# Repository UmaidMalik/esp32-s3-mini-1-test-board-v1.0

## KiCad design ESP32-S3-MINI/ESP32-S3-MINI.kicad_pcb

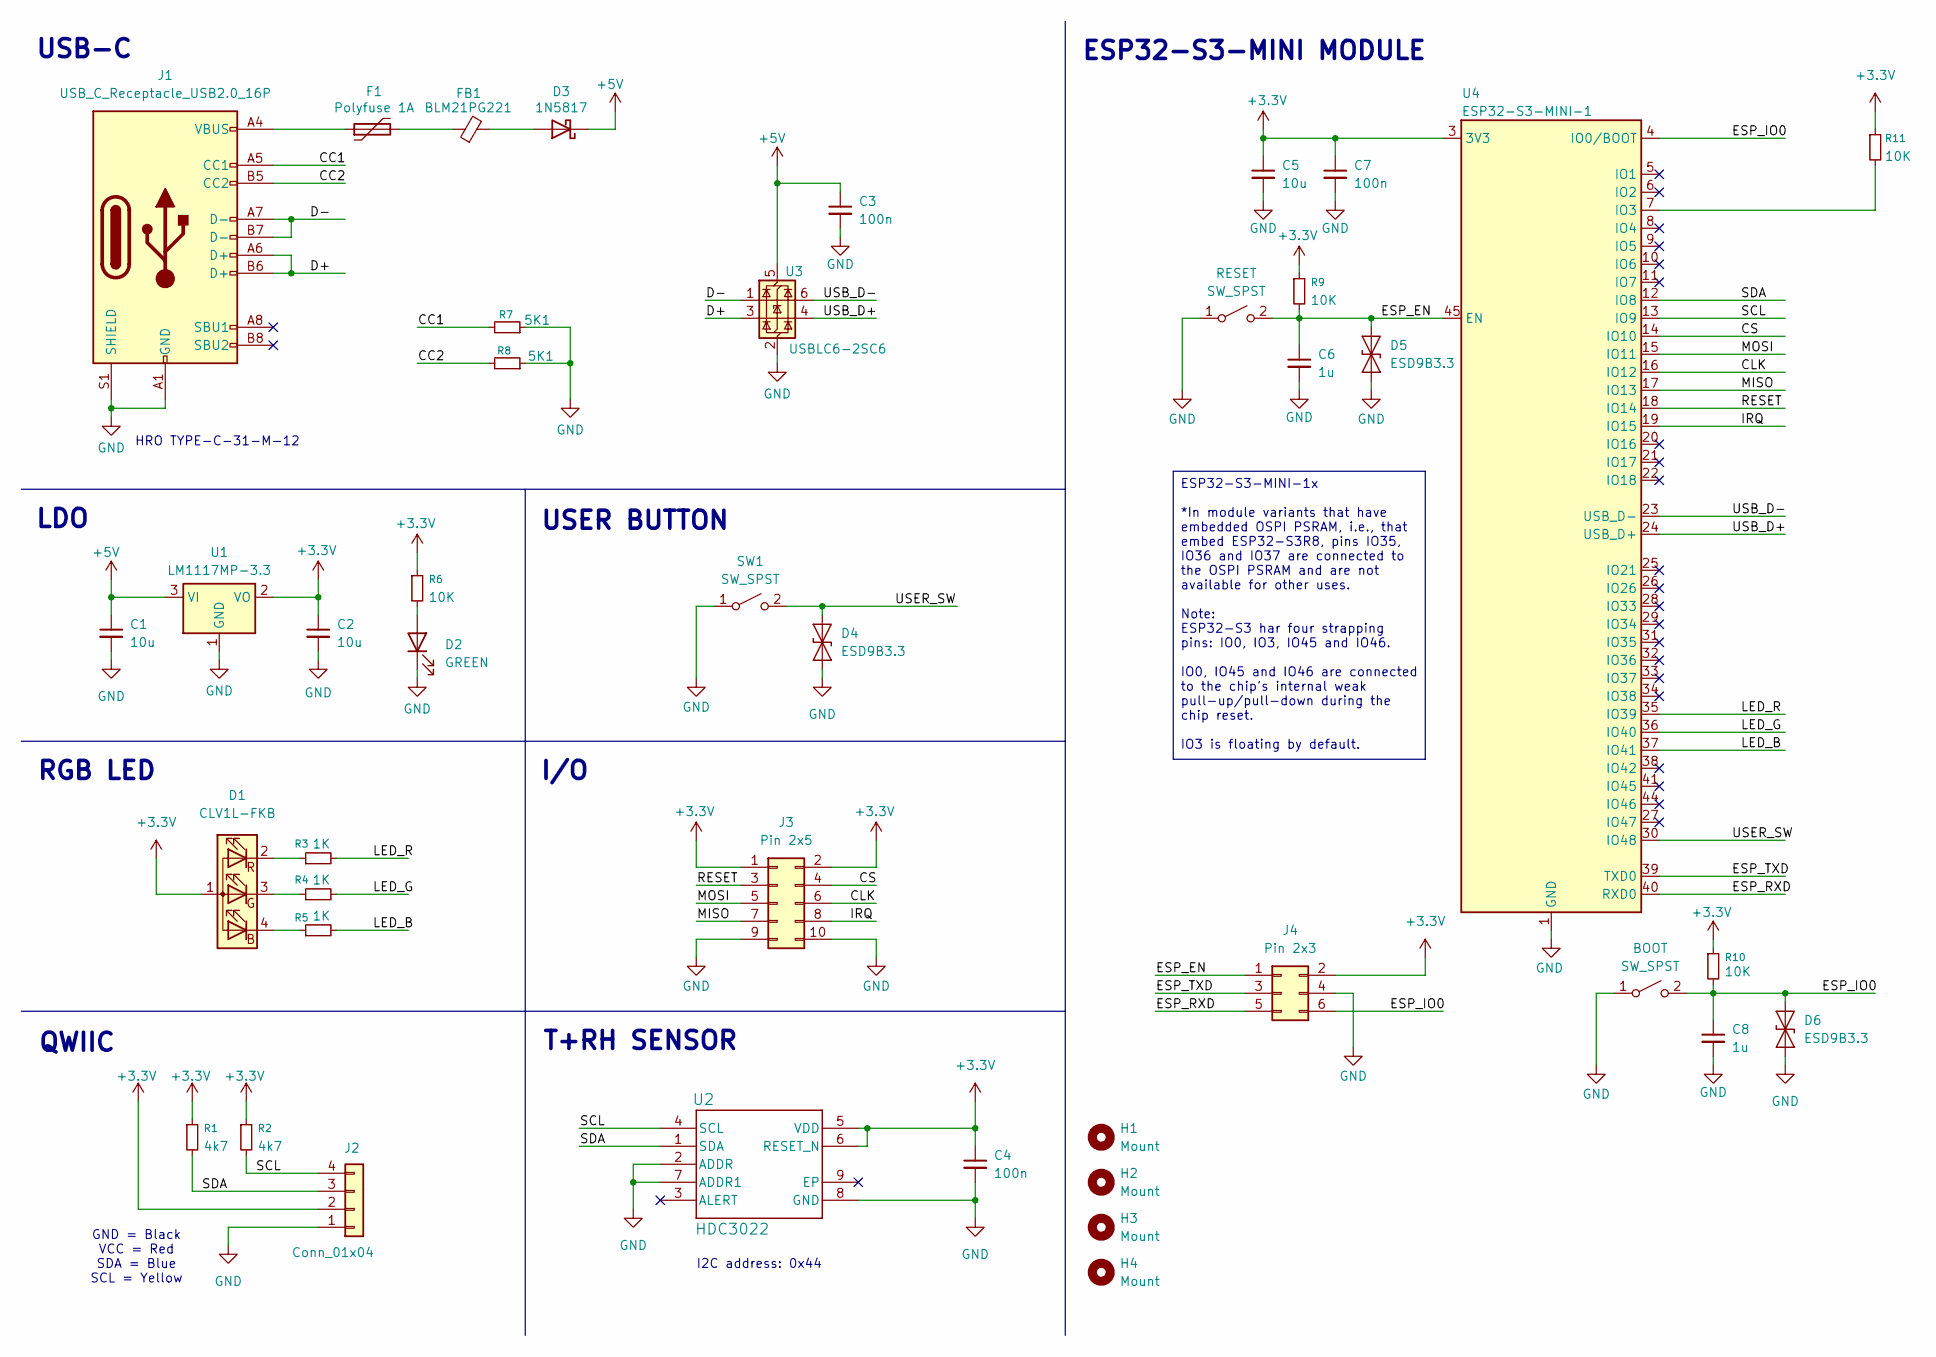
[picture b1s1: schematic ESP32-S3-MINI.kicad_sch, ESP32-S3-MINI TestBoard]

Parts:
BOOT: SW_SPST; SW_SPST_B3U-1000P
C1, C2, C5: 10u; C_0603_1608Metric
C3, C4, C7: 100n; C_0402_1005Metric
C6, C8: 1u; C_0603_1608Metric
D1: CLV1L-FKB; LED_Cree-PLCC4_3.2x2.8mm_CCW
D2: GREEN; LED_0603_1608Metric
D3: 1N5817; D_MiniMELF
D4, D5, D6: ESD9B3.3; D_SOD-923
F1: Polyfuse 1A; Fuse_1206_3216Metric_Pad1.42x1.75mm_HandSolder
FB1: BLM21PG221; L_0805_2012Metric
H1, H2, H3, H4: Mount; MountingHole_3.2mm_M3_DIN965
J1: USB_C_Receptacle_USB2.0_16P; USB_C_Receptacle_HRO_TYPE-C-31-M-12
J2: Conn_01x04; JST_SH_SM04B-SRSS-TB_1x04-1MP_P1.00mm_Horizontal
J3: Pin 2x5; PinHeader_2x05_P2.54mm_Vertical
J4: Pin 2x3; PinHeader_2x03_P2.54mm_Vertical
R1, R2: 4k7; R_0402_1005Metric
R3, R4, R5: 1K; R_0402_1005Metric
R6, R9, R10, R11: 10K; R_0402_1005Metric
R7, R8: 5K1; R_0402_1005Metric
RESET: SW_SPST; SW_SPST_B3U-1000P
SW1: SW_SPST; SW_Tactile_SPST_Angled_PTS645Vx31-2LFS
U1: LM1117MP-3.3; SOT-223-3_TabPin2
U2: HDC3022; DEJ0008A-C01-MFG
U3: USBLC6-2SC6; SOT-23-6
U4: ESP32-S3-MINI-1; XCVR_ESP32-S3-MINI-1-N8

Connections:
+3.3V: C2.1, C4.1, C5.1, C7.1, D1.1 (A), J2.2, J3.1, J3.2, J4.2, R1.1, R2.1, R6.1, R9.1, R10.1, R11.1, U1.2 (VO), U2.5 (VDD), U2.6 (RESET_N), U4.3 (3V3)
+5V: C1.1, C3.1, D3.1 (K), U1.3 (VI), U3.5 (VBUS)
/CC1: J1.A5 (CC1), R7.2
/CC2: J1.B5 (CC2), R8.2
/CLK: J3.6, U4.16 (IO12)
/CS: J3.4, U4.14 (IO10)
/D+: J1.A6 (D+), J1.B6 (D+), U3.3 (I/O2)
/D-: J1.A7 (D-), J1.B7 (D-), U3.1 (I/O1)
/ESP_EN: C6.1, D5.1 (A1), J4.1, R9.2, RESET.2 (B), U4.45 (EN)
/ESP_IO0: BOOT.2 (B), C8.1, D6.1 (A1), J4.6, R10.2, U4.4 (IO0/BOOT)
/ESP_RXD: J4.5, U4.40 (RXD0)
/ESP_TXD: J4.3, U4.39 (TXD0)
/IRQ: J3.8, U4.19 (IO15)
/LED_B: R5.2, U4.37 (IO41)
/LED_G: R4.2, U4.36 (IO40)
/LED_R: R3.2, U4.35 (IO39)
/MISO: J3.7, U4.17 (IO13)
/MOSI: J3.5, U4.15 (IO11)
/RESET: J3.3, U4.18 (IO14)
/SCL: J2.4, R2.2, U2.4 (SCL), U4.13 (IO9)
/SDA: J2.3, R1.2, U2.1 (SDA), U4.12 (IO8)
/USB_D+: U3.4 (I/O2), U4.24 (USB_D+)
/USB_D-: U3.6 (I/O1), U4.23 (USB_D-)
/USER_SW: D4.1 (A1), SW1.2 (B), U4.30 (IO48)
GND: BOOT.1 (A), C1.2, C2.2, C3.2, C4.2, C5.2, C6.2, C7.2, C8.2, D2.1 (K), D4.2 (A2), D5.2 (A2), D6.2 (A2), J1.A1 (GND), J1.A12 (GND), J1.B1 (GND), J1.B12 (GND), J1.S1 (SHIELD), J2.1, J3.9, J3.10, J4.4, R7.1, R8.1, RESET.1 (A), SW1.1 (A), U1.1 (GND), U2.2 (ADDR), U2.7 (ADDR1), U2.8 (GND), U3.2 (GND), U4.1 (GND)
unnamed: D1.4 (BK), R5.1
unnamed: D1.3 (GK), R4.1
unnamed: D1.2 (RK), R3.1
unnamed: D2.2 (A), R6.2
unnamed: D3.2 (A), FB1.2
unnamed: F1.1, J1.A4 (VBUS), J1.A9 (VBUS), J1.B4 (VBUS), J1.B9 (VBUS)
unnamed: F1.2, FB1.1
unnamed: U4.2 (GND), U4.42 (GND), U4.43 (GND), U4.46 (GND), U4.47 (GND), U4.48 (GND), U4.49 (GND), U4.50 (GND), U4.51 (GND), U4.52 (GND), U4.53 (GND), U4.54 (GND), U4.55 (GND), U4.56 (GND), U4.57 (GND), U4.58 (GND), U4.59 (GND), U4.60 (GND), U4.61 (GND), U4.62 (GND), U4.63 (GND), U4.64 (GND), U4.65 (GND)
unnamed: R11.2, U4.7 (IO3)

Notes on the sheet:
I/O
T+RH SENSOR
I2C address: 0x44
GND = Black VCC = Red SDA = Blue SCL = Yellow
ESP32-S3-MINI MODULE
USER BUTTON
LDO
QWIIC
RGB LED
USB-C
HRO TYPE-C-31-M-12
ESP32-S3-MINI-1x *In module variants that have embedded OSPI PSRAM, i.e., that embed ESP32-S3R8, pins IO35, IO36 and IO37 are connected to the OSPI PSRAM and are not available for other uses. Note: ESP32-S3 har four strapping pins: IO0, IO3, IO45 and IO46. IO0, IO45 and IO46 are connected to the ch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

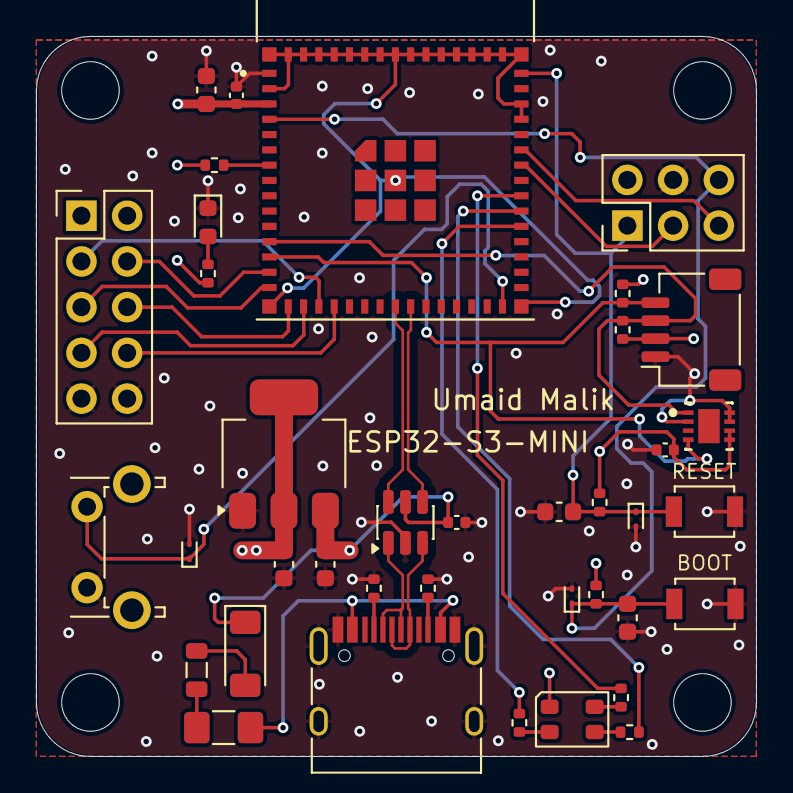
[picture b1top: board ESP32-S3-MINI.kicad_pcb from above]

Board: 4 copper layers, 40.0 x 40.0 mm, 42 parts (0 on the bottom side), 34 nets.
